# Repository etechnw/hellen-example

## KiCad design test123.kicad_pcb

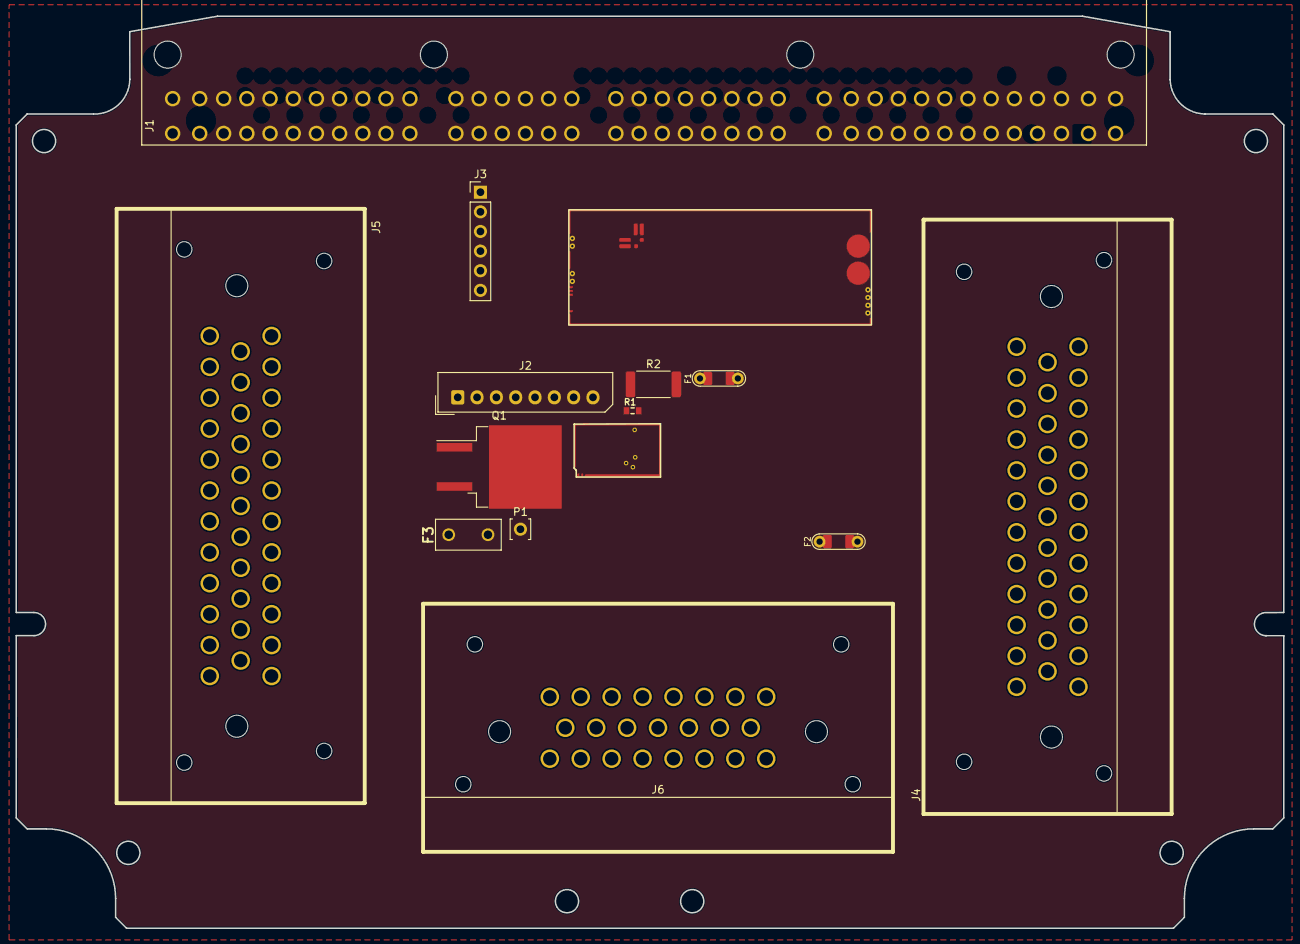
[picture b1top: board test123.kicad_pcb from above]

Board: 2 copper layers, 164.0 x 118.0 mm, 15 parts (0 on the bottom side), 21 nets, no tracks yet.

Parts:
F1, F2: Fuse-Pad-Pad; PAD-1206-PAD
F3: 10A; 36911600000
J1: TE-3-178780-6
J2: XH-8A
J3: Conn_01x06; PinHeader_1x06_P2.54mm_Vertical
J4: Conn_01x35; ampseal-35
J5: Conn_01x35; ampseal-35-2
J6: Conn_01x23; ampseal-23
M1: Module-wbo-0.2; wbo
M2: Module-can-0.1; can
P1: Pad; PAD-TH
Q1: ISL9V3040S3S; TO-263-2
R1: 22; R0603
R2: DNP; R_2512_6332Metric

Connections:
/5V_SENSOR_1: J5.9, J5.21, J5.32
/5V_SENSOR_2: J5.10, J5.22, J5.33, M1.W1 (V5_IN), M2.V1 (V5)
/12V_MR: F1.2, F2.2, J6.23
/12V_PROT: J5.11, J5.12
/GATE_IGN1: R1.2, R2.1
/OUT_IGN1: F3.2, Q1.2 (C), R2.2
/WBO_H-: J2.3, J2.4, M1.E5 (LSU_H+)
/WBO_Ip: J2.6, M1.E3 (LSU_Ip)
/WBO_R_Trim: J2.5, M1.E4 (LSU_Rtrim)
/WBO_Vs: J2.8, M1.E1 (LSU_Un)
/WBO_Vs/Ip: J2.7, M1.E2 (LSU_Vm)
GND: J2.1, J2.2, J3.3, J4.17, J4.18, J4.24, J5.1, J5.2, J5.3, J5.4, J5.5, J5.6, J5.7, J5.8, J5.23, J5.29, J6.14, J6.19, J6.20, M1.E6 (LSU_H-), M1.G (GND), M2.E1 (GND), Q1.3 (E)
unnamed: J3.1, M1.W8 (V33_OUT)
unnamed: J3.2, M1.W7 (SWCLK)
unnamed: J3.4, M1.W6 (SWDIO)
unnamed: J3.5, M1.W5 (nReset)
unnamed: M1.J1 (SEL1), M1.J_GND1 (PULL_DOWN1)
unnamed: M1.W2 (CAN_VIO), M2.V2 (CAN_VIO)
unnamed: M1.W3 (CAN_RX), M2.V6 (CAN_RX)
unnamed: M1.W4 (CAN_TX), M2.V5 (CAN_TX)
unnamed: Q1.1 (G), R1.1

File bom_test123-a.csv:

"#","Reference","Qty","Value","Footprint","DNP"
"1","F1, F2","2","Fuse-Pad-Pad","hellen-one-common:PAD-1206-PAD",""
"2","F3","1","10A","hellen-one-common:36911600000",""
"3","J1","1","TE-3-178780-6","lib:TE-3-178780-6",""
"4","J2","1","XH-8A","hellen-one-common:XH-8A",""
"5","J3","1","Conn_01x06","Connector_PinHeader_2.54mm:PinHeader_1x06_P2.54mm_Vertical",""
"6","J4","1","Conn_01x35","lib:ampseal-35",""
"7","J5","1","Conn_01x35","lib:ampseal-35-2",""
"8","J6","1","Conn_01x23","lib:ampseal-23",""
"9","M1","1","Module-wbo-0.2","hellen-one-wbo-0.2:wbo",""
"10","M2","1","Module-can-0.1","hellen-one-can-0.1:can",""
"11","P1","1","Pad","hellen-one-common:PAD-TH",""
"12","Q1","1","ISL9V3040S3S","Package_TO_SOT_SMD:TO-263-2",""
"13","R1","1","22","hellen-one-common:R0603",""
"14","R2","1","DNP","Resistor_SMD:R_2512_6332Metric",""

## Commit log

2024-01-11 test
2024-01-11 [skip actions] Auto-generated board v2.1
